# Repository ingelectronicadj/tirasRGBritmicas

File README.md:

# Tiras de leds RGB ritmicas
Este proyecto tiene como proposito iluminar un ambiente de acuerdo al ritmo de la música.

# Materiales
* Tira de leds RGB de 5mts
* Microcontrolador Atmega328
* Transistores NPN de potencia
* Sensor de sonido
* Crsital de 16MHz, condensadores de 22pF, resistencias

# Diseño PCB

# Fases de trabajo
* Fase 1: Realizar secuencias de blink(parpadeo), brillo(intensidad) **(Done)**
* Fase 2: Ritmicas On/Off de colores RGB, CMY de acuerdo al sobrepaso de un nivel de volumen. **(Done)**
* Fase 3: Ritmicas por frecuencias del audio.

Hilo útil para la fase 3: https://www.arduino.cc/en/Tutorial/SimpleAudioFrequencyMeter

###Desarrollador
* Diego Javier Mena - @ingelectronicadj

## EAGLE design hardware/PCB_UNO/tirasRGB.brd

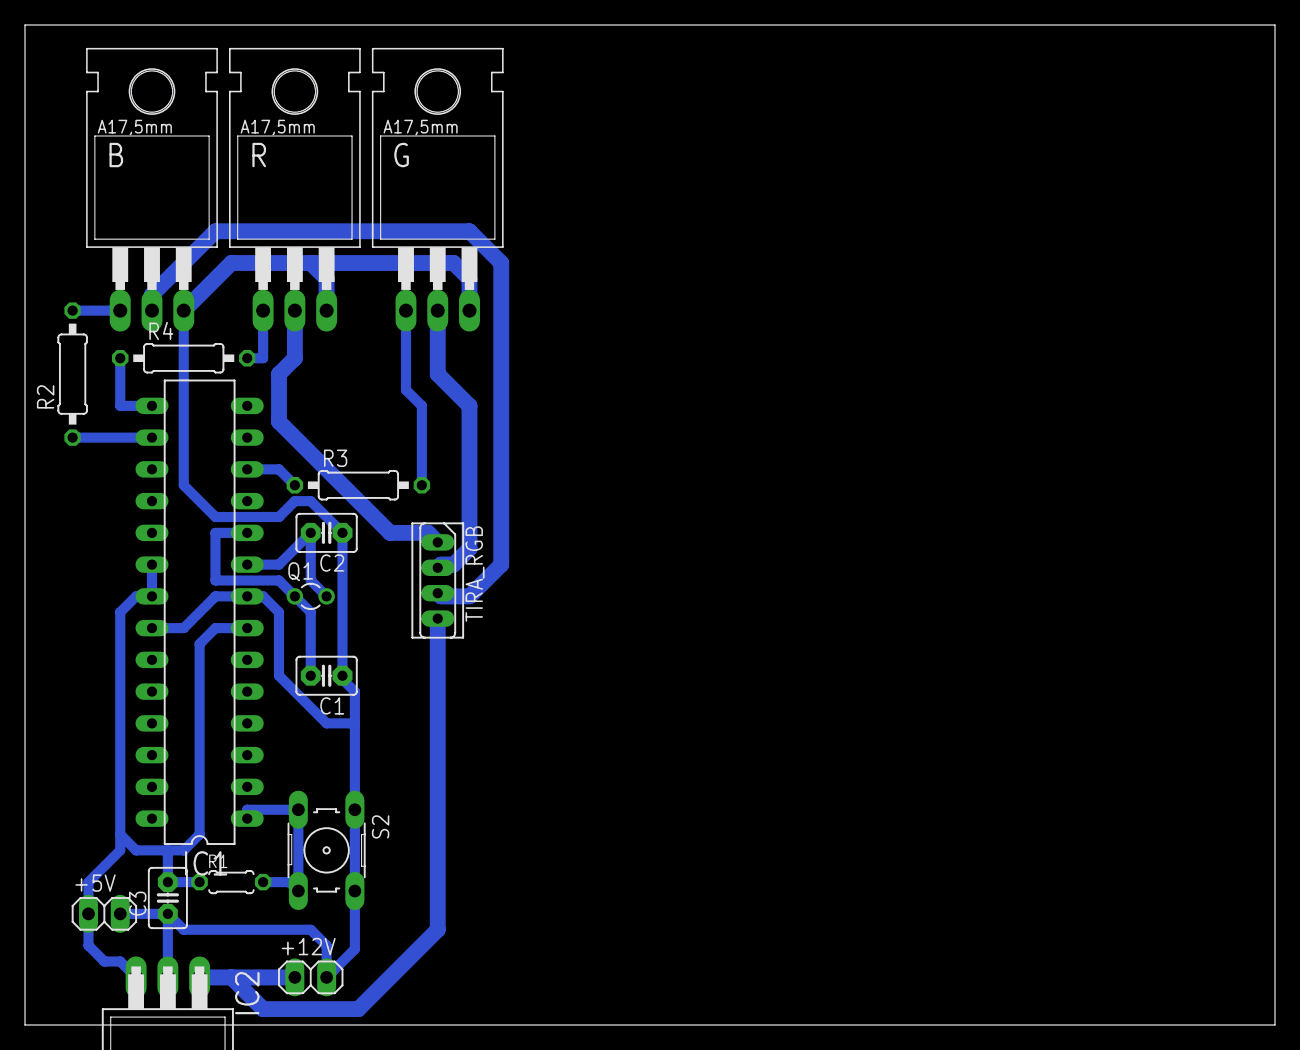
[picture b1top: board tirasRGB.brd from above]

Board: 2 copper layers, 100.0 x 80.0 mm, 17 parts (0 on the bottom side), 15 nets.

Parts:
+5V, +12V: 1X02
B: 2N5496; TO220
C1, C2, C3: C2.5-3
G: 2N5496; TO220
IC1: MEGA8-P; DIL28-3
IC2: 7805T; TO220H
Q1: TC26V
R: 2N5496; TO220
R1: 0204/5
R2, R3, R4: 0207/10
S2: B3F-10XX
TIRA_RGB: SPB4

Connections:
3.3V: +5V.1, C3.2, IC1.7, IC1.20, IC1.21, IC2.3, R1.1
GND: +5V.2, +12V.2, B.3, C1.1, C2.1, C3.1, G.3, IC1.8, IC1.22, IC2.2, R.3, S2.1, S2.2
unnamed: B.1, R2.2
unnamed: +12V.1, IC2.1, TIRA_RGB.4
unnamed: G.1, R3.2
unnamed: R.1, R4.2
unnamed: R.2, TIRA_RGB.1
unnamed: G.2, TIRA_RGB.2
unnamed: B.2, TIRA_RGB.3
unnamed: IC1.15, R4.1
unnamed: IC1.12, R3.1
unnamed: IC1.16, R2.1
unnamed: C2.2, IC1.9, Q1.2
unnamed: C1.2, IC1.10, Q1.1
unnamed: IC1.1, R1.2, S2.3, S2.4

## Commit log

2016-12-16 Se añade codigo base para lectura del sensor de sonido
2016-12-16 Se añaden lineas para la respectiva prueba de cada canal RGB y del sensor de volumen de sonido
2016-12-16 Se recuerda reutilizar la funcion de blink para pruebas y se calibra el sensor para que sea sensible a sobrepasos de un valor analogico determinado
2016-12-16 Se añade un contador para cambiar colores de la tira RGB dentro de la funcion picoDeSonido
2016-12-17 Se aplica un contador para realizar blink con cambio de color RGB cada 6 picos de sonido
2016-12-17 Se añade cto esquematico hecho con fritzing
2016-12-17 Se añade sensor de sonido al esquematico
2016-12-18 Se añade funcion para controlar el brillo y se añade titileo de los colores secundarios CMY Cian-Magenta-Yellow
2016-12-18 Se realizan cambios al esquematico y se añade una imagen para realizar conexiones
2016-12-18 Esquema hecho en fritzing
2016-12-18 Se añade rutina de brillos
2016-12-18 Se añade libreria de audioFrecuencia y se modifica el readme
2016-12-18 Se añade diseño PCB base(Atmega328) hecho en eagle
2016-12-19 Se extiende posibilidad de colores para la funcion pico de sonido
2016-12-19 Se cambia regulador del diseño PCB y se eliminan ficheros generados por la impresora de PCB
2016-12-19 Se arreglan bugs de las funciones de brillo y se modifican tiempos de transicion
2016-12-20 Se añade circuito de potencia al diseño PCB y se dejan las pistas un poco mas amplias que para el cto de control
2016-12-25 Se mejora PCB de diseño
2017-01-01 Se añade sensor de sonido 3 pines
